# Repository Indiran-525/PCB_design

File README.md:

# PCB_design

This repository contains my PCB design for basic circuits out there in the open

All the circuits were designed using Kicad

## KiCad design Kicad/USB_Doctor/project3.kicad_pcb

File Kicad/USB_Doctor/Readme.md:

This is a basic usb doctor/charging monitor that measures and displays the voltage, current and power that is being drawn through, It consits of a male USB A connector on one end which can
be connected to adapters and the device has a female USB A connector on other end to which the device to be charged can be plugged in.

## Components:
  1. Atmega328p
  2. Ina219 sensor
  3. 10k resistors
  4. ams1117 3.3v voltage regulator
  5. usb connectors
  6. capacitor - 100nf

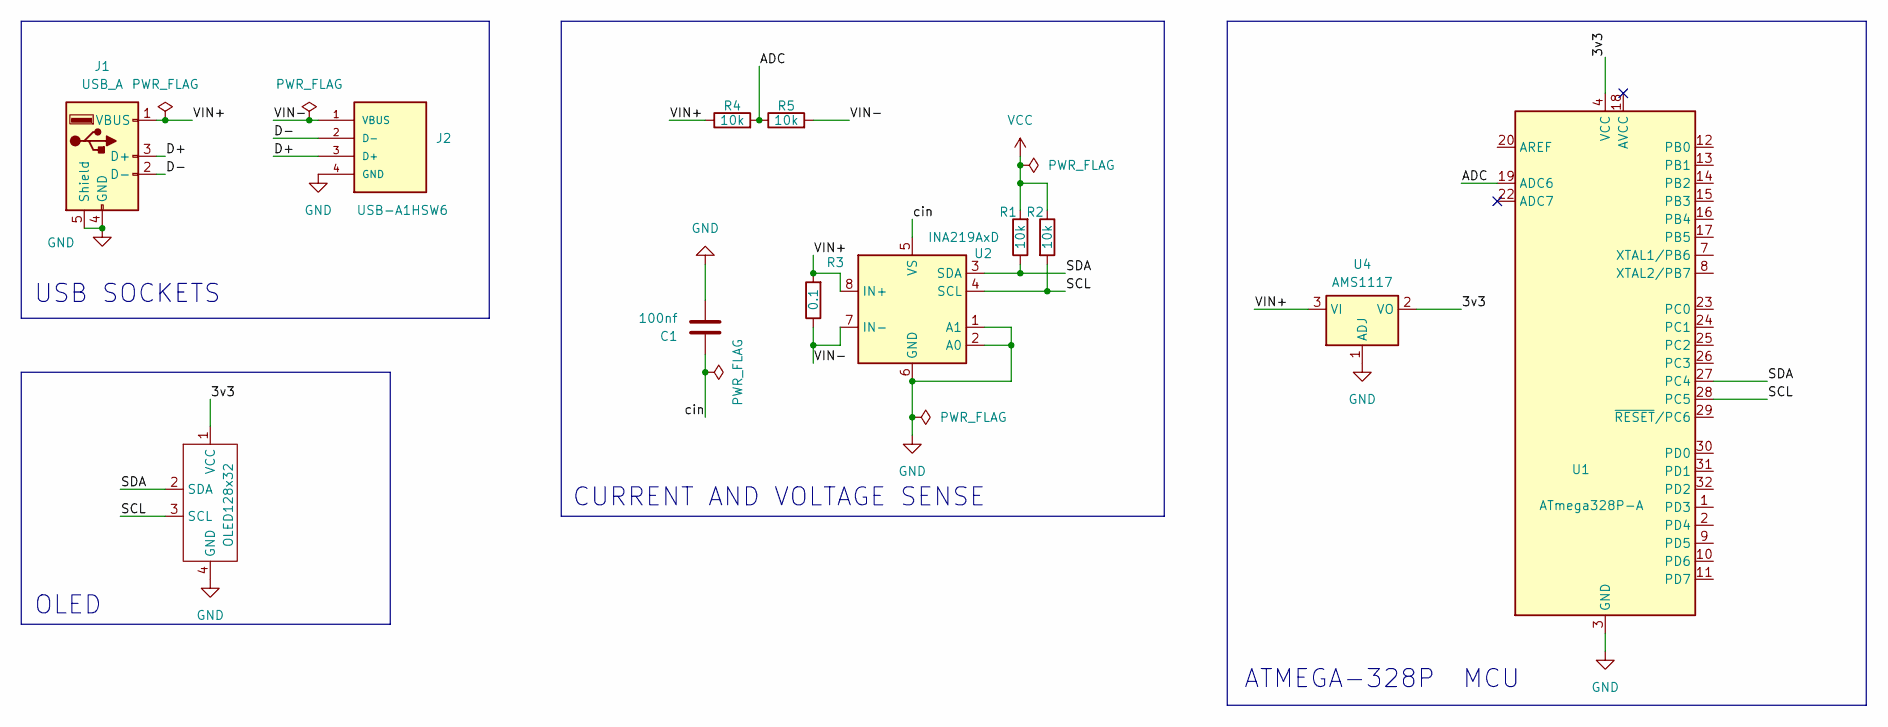
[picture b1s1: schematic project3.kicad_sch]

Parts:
C1: 100nf; CP_Elec_4x3
J1: USB_A; USB_A_CNCTech_1001-011-01101_Horizontal
J2: USB-A1HSW6; OST_USB-A1HSW6; PARTREV A
OLED128x32: SSD1306-0.91-OLED-4pin-128x32
R1, R2, R4, R5: 10k; R_0201_0603Metric_Pad0.64x0.40mm_HandSolder
R3: 0.1; R_0201_0603Metric_Pad0.64x0.40mm_HandSolder
U1: ATmega328P-A; TQFP-32_7x7mm_P0.8mm
U2: INA219AxD; SOIC-8_3.9x4.9mm_P1.27mm
U4: AMS1117; SOT-223-3_TabPin2

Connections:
/3v3: OLED128x32.1 (VCC), U1.4 (VCC), U1.6 (VCC), U4.2 (VO)
/ADC: R4.2, R5.1, U1.19 (ADC6)
/D+: J1.3 (D+), J2.3 (D+)
/D-: J1.2 (D-), J2.2 (D-)
/SCL: OLED128x32.3 (SCL), R2.2, U1.28 (PC5), U2.4 (SCL)
/SDA: OLED128x32.2 (SDA), R1.1, U1.27 (PC4), U2.3 (SDA)
/VIN+: J1.1 (VBUS), R3.2, R4.1, U2.8 (IN+), U4.3 (VI)
/VIN-: J2.1 (VBUS), R3.1, R5.2, U2.7 (IN-)
/cin: C1.1, U2.5 (VS)
GND: C1.2, J1.4 (GND), J1.5 (Shield), J2.4 (GND), OLED128x32.4 (GND), U1.3 (GND), U1.5 (GND), U1.21 (GND), U2.1 (A1), U2.2 (A0), U2.6 (GND), U4.1 (ADJ)
VCC: R1.2, R2.1

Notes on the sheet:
USB SOCKETS
OLED
ATMEGA-328P MCU
CURRENT AND VOLTAGE SENSE

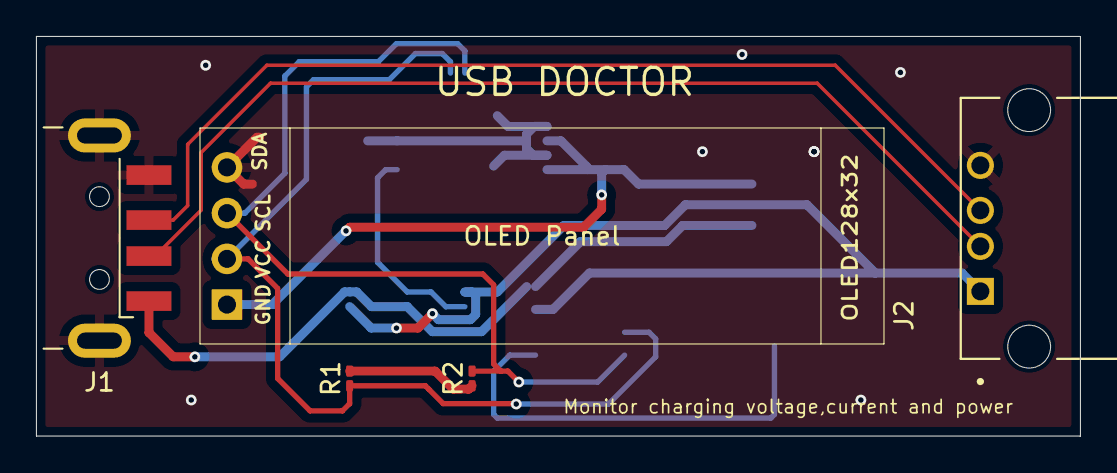
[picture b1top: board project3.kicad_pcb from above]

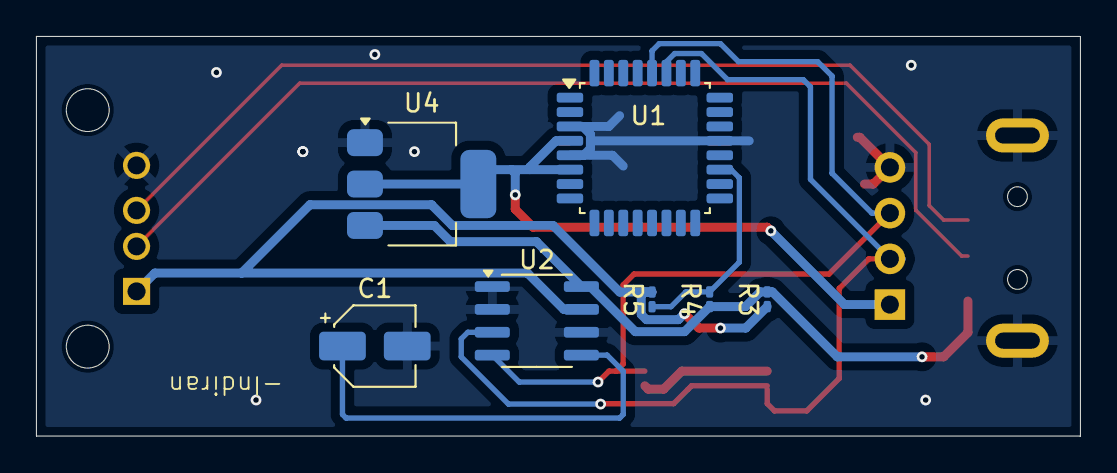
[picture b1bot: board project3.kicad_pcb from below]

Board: 2 copper layers, 58.0 x 22.2 mm, 12 parts (7 on the bottom side), 11 nets.

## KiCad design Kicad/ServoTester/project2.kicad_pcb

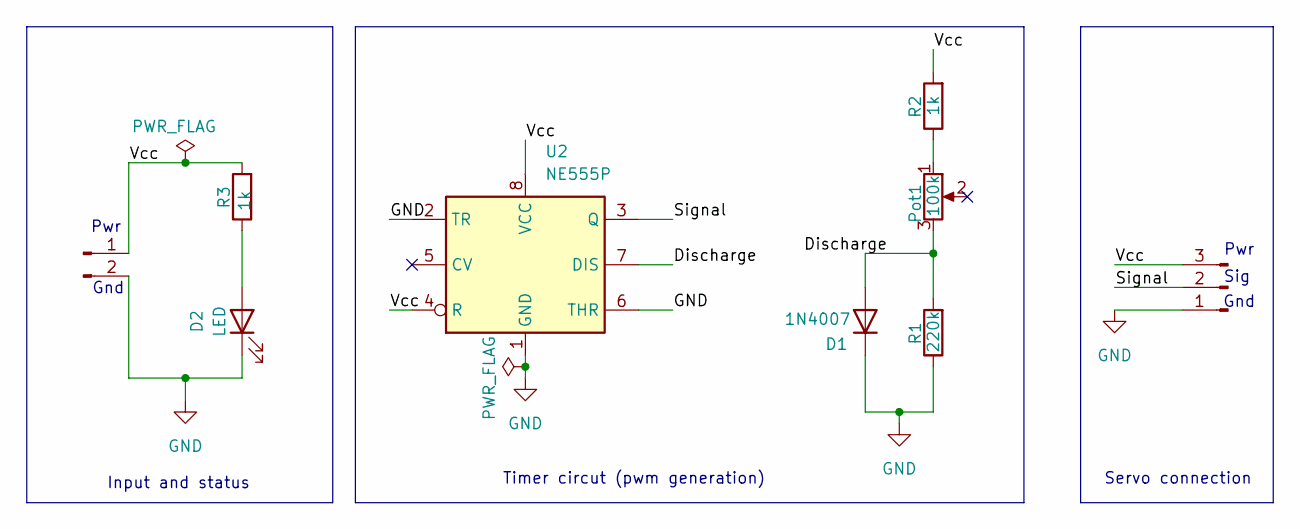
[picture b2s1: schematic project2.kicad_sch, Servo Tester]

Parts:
D1: 1N4007; D_DO-41_SOD81_P10.16mm_Horizontal
D2: LED; LED_D3.0mm
J1: Power; PinHeader_1x02_P1.27mm_Horizontal
J2: Servo; PinHeader_1x03_P1.27mm_Horizontal
Pot1: 100k; Potentiometer_Alps_RK09Y11_Single_Horizontal
R1: 220k; R_Axial_DIN0309_L9.0mm_D3.2mm_P12.70mm_Horizontal
R2, R3: 1k; R_Axial_DIN0309_L9.0mm_D3.2mm_P12.70mm_Horizontal
U2: NE555P; DIP-8_W7.62mm

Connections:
/Discharge: D1.2 (A), Pot1.3, R1.2, U2.7 (DIS)
/Signal: J2.2, U2.3 (Q)
/Vcc: J1.1, J2.3, R2.2, R3.2, U2.4 (R), U2.8 (VCC)
GND: D1.1 (K), D2.1 (K), J1.2, J2.1, R1.1, U2.1 (GND), U2.2 (TR), U2.6 (THR); also elsewhere on the board
unnamed: D2.2 (A), R3.1
unnamed: Pot1.1, R2.1

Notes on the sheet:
Sig
Gnd
Timer circut (pwm generation)
Servo connection
Pwr
Input and status

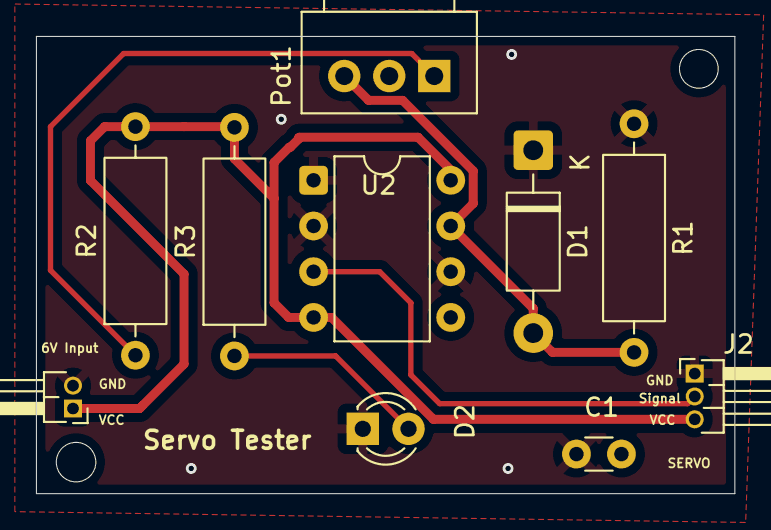
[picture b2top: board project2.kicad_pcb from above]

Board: 2 copper layers, 38.8 x 25.4 mm, 10 parts (0 on the bottom side), 6 nets.

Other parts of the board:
C1: 100nf; C_Disc_D3.0mm_W1.6mm_P2.50mm

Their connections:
GND: C1.1; also elsewhere on the board

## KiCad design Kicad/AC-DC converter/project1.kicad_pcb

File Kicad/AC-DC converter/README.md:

# AC-DC-Converter

This is a basic Ac to Dc converter circuit, that takes in 230v AC as iniput and converts it into 5v dc as output. The flow of conversion is as follows:

230v i/p --> transformer --> bridge rectifier --> voltage regulator --> zener diode --> output

A capacitor is used at the input for coupling and a few intermediate capacitors are used for filtering purposes.

## components used:

1. 240 - 12v setp down transformer
2. IN4001 diodes
3. Capacitors
4. Zener diode
5. Voltage regulator LM7805
6. Resistors
7. Led

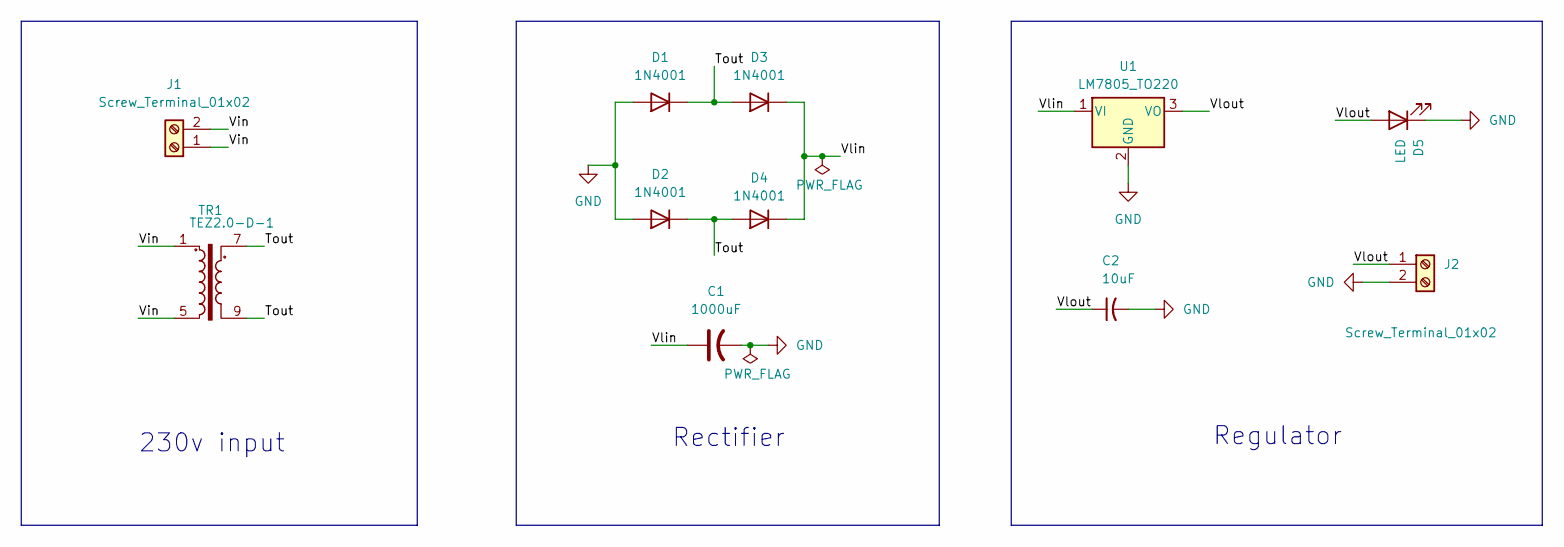
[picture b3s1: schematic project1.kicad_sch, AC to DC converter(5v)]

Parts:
C1: 1000uF; C_Radial_D12.5mm_H25.0mm_P5.00mm
C2: 10uF; C_Disc_D7.5mm_W4.4mm_P5.00mm
D1, D2, D3, D4: 1N4001; D_DO-41_SOD81_P10.16mm_Horizontal
D5: LED; LED_D1.8mm_W1.8mm_H2.4mm_Horizontal_O1.27mm_Z1.6mm
J1, J2: Screw_Terminal_01x02; TerminalBlock_MaiXu_MX126-5.0-02P_1x02_P5.00mm
TR1: TEZ2.0-D-1; Transformer_Breve_TEZ-28x33
U1: LM7805_TO220; TO-220-3_Vertical

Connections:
/Tout: D1.1 (K), D2.1 (K), D3.2 (A), D4.2 (A), TR1.7, TR1.9
/Vin: J1.1, J1.2, TR1.1, TR1.5
/Vlin: C1.1, D3.1 (K), D4.1 (K), U1.1 (VI)
/Vlout: C2.1, D5.2 (A), J2.1, U1.3 (VO); also elsewhere on the board
GND: C1.2, C2.2, D1.2 (A), D2.2 (A), D5.1 (K), J2.2, U1.2 (GND); also elsewhere on the board

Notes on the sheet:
Rectifier
230v input
Regulator

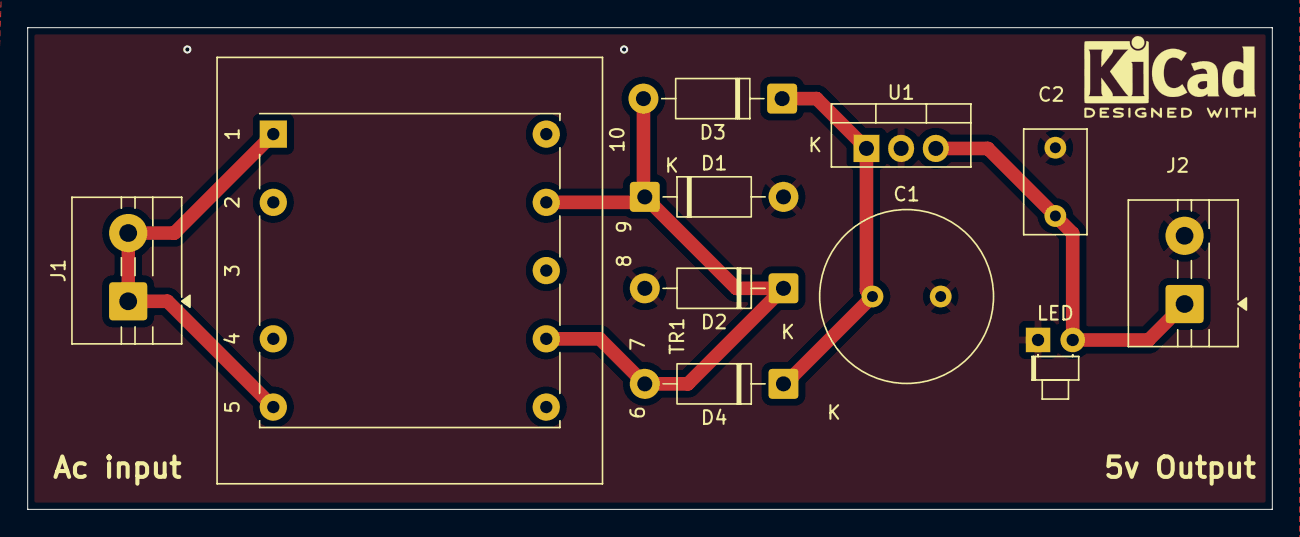
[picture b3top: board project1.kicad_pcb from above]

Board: 2 copper layers, 91.2 x 35.3 mm, 11 parts (0 on the bottom side), 5 nets.

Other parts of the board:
LED: LED; LED_D1.8mm_W1.8mm_H2.4mm_Horizontal_O1.27mm_Z1.6mm

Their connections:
/Vlout: LED.2 (A); also elsewhere on the board
GND: LED.1 (K); also elsewhere on the board

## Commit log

2025-06-20 kicad
2025-07-30 Rename Readme to Readme.md
